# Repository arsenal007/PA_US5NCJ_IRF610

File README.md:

# PA_US5NCJ_IRF610
Power Amplifier US5NCJ

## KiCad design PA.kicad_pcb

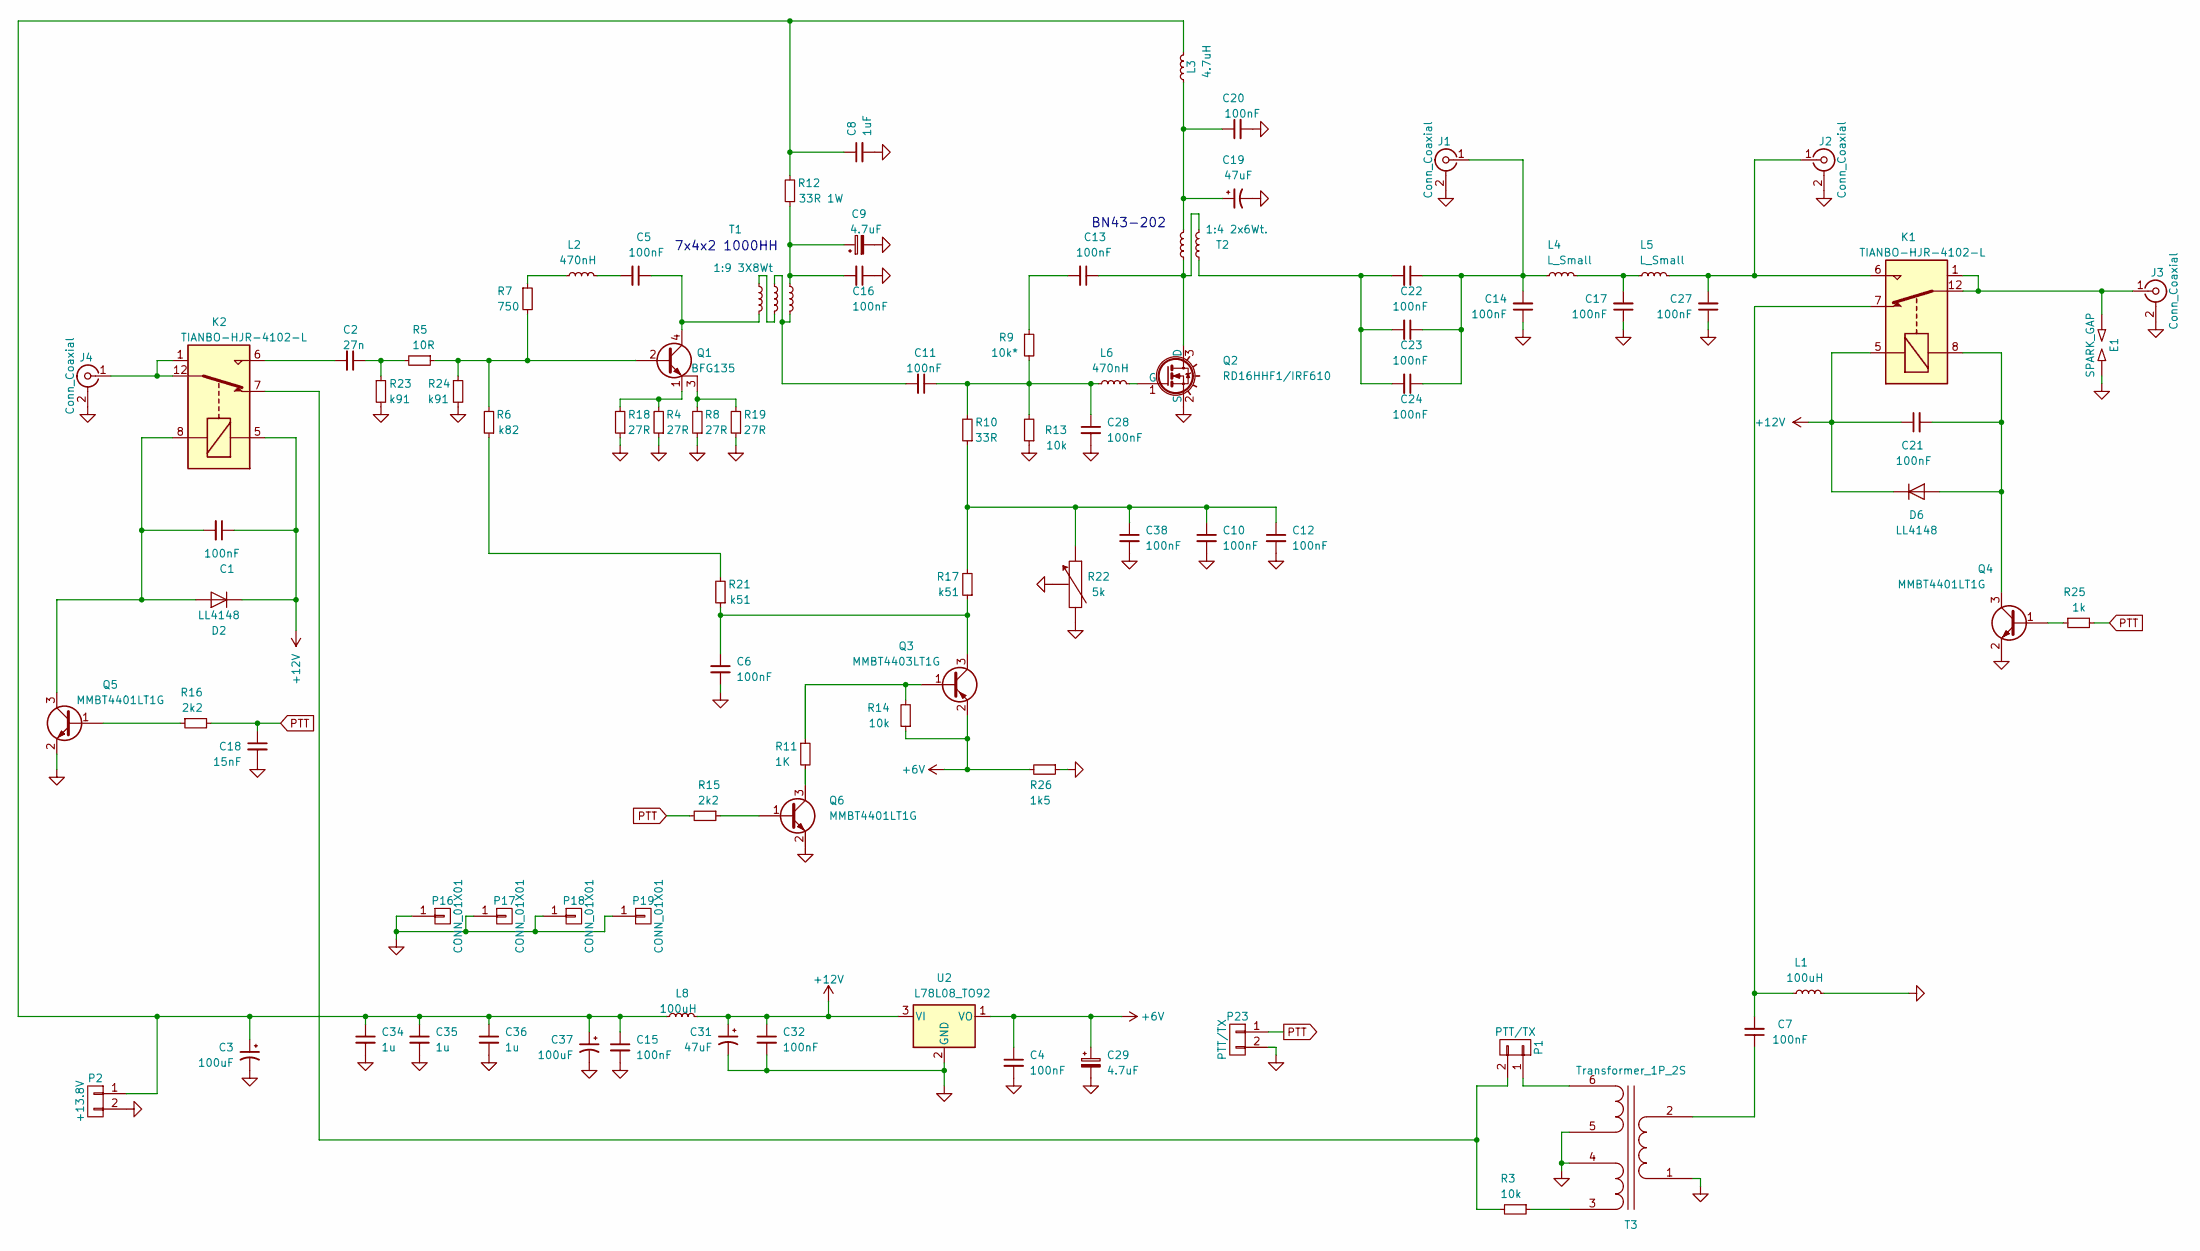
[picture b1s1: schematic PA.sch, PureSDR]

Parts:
C1, C4, C5, C6, C7, C10, C11, C12, C13, C14, C15, C16, C17, C20, C21, C22, C23, C24, C27, C28, C32, C38: 100nF; C_1206_0603
C2: 27n; C_1206_0603
C3, C37: 100uF; CP_Tantalum_Case-D_EIA-7343-31_Hand
C8: 1uF; C_1206_0603
C9, C29: 4.7uF; CP_Tantalum_Case-A_EIA-3216-18_Hand
C18: 15nF; C_1206_0603
C19, C31: 47uF; c_elec_6.3x7.7
C34, C35, C36: 1u; C_1206_0603
D2, D6: LL4148; MiniMELF_Handsoldering
E1: SPARK_GAP; Resistor_Horizontal_RM10mm
J1, J2, J3, J4: Conn_Coaxial; RFCONNECTOR
K1, K2: TIANBO-HJR-4102-L; Relay_SPDT_HJR-4102
L1, L8: 100uH; Resistor_SMD+THTuniversal_0805to2512_RM10_HandSoldering
L2, L6: 470nH; Resistor_SMD+THTuniversal_0805to2512_RM10_HandSoldering
L3: 4.7uH; Choke_CD54
L4, L5: L_Small; Choke_Toroid_horizontal_Diameter14mm_Amidon-T50
P1: PTT/TX; Pin_Header_Angled_1x02_Pitch2.54mm
P2: +13.8V; TerminalBlock_bornier-2_P5.08mm
P16, P17, P18, P19: CONN_01X01; MountingHole_3.2mm_M3_ISO7380_Pad
P23: PTT/TX; Pin_Header_Straight_1x02
Q1: BFG135; SOT-223
Q2: RD16HHF1/IRF610; RD16HHF1
Q3: MMBT4403LT1G; SOT-23_Handsoldering
Q4, Q5, Q6: MMBT4401LT1G; SOT-23_Handsoldering
R3, R13, R14: 10k; R_1206_0603
R4, R8, R18, R19: 27R; R_1206_0603
R5: 10R; R_1206_0603
R6: k82; R_1206_0603
R7: 750; R_1206_0603
R9: 10k*; Resistor_SMD+THTuniversal_0805to2512_RM10_HandSoldering
R10: 33R; R_1206_0603
R11: 1K; R_1206_0603
R12: 33R 1W; Resistor_SMD+THTuniversal_0805to2512_RM10_HandSoldering
R15, R16: 2k2; R_1206_0603
R17, R21: k51; R_1206_0603
R22: 5k; Potentiometer_Bourns_3296W_3-8Zoll_Inline_ScrewUp
R23, R24: k91; R_1206_0603
R25: 1k; R_1206_0603
R26: 1k5; R_1206_0603
T1: 1:9 3X8Wt; HF12
T2: 1:4 2x6Wt.; TRANSF1_4
T3: Transformer_1P_2S; Transf1_9
U2: L78L08_TO92; TO-92_Inline_Wide

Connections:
+6V: C4.1, C29.1, Q3.2 (E), R14.1, R26.2, U2.1 (VO)
+12V: C1.1, C21.1, C31.1, C32.1, D2.1 (K), D6.1 (K), K1.5, K2.5, L8.2, U2.3 (VI)
GND: C3.2, C4.2, C6.2, C8.2, C9.2, C10.2, C12.2, C14.1, C15.2, C16.1, C17.1, C18.2, C19.2, C20.2, C27.1, C28.2, C29.2, C31.2, C32.2, C34.2, C35.2, C36.2, C37.2, C38.2, E1.2, J1.2 (Ext), J2.2 (Ext), J3.2 (Ext), J4.2 (Ext), L1.2, P2.2, P16.1, P17.1, P18.1, P19.1, P23.2, Q2.2 (S), Q4.2 (E), Q5.2 (E), Q6.2 (E), R4.1, R8.1, R13.1, R18.1, R19.1, R22.2, R22.3, R23.2, R24.2, R26.1, T3.1 (AA), T3.4 (SB), T3.5 (SC), U2.2 (GND)
unnamed: C1.2, D2.2 (A), K2.8, Q5.3 (C)
unnamed: C2.1, R5.2, R23.1
unnamed: C2.2, K2.6
unnamed: C5.1, Q1.4 (C), T1.2
unnamed: C5.2, L2.2
unnamed: C6.1, Q3.3 (C), R17.1, R21.1
unnamed: C7.1, T3.2 (AB)
unnamed: C7.2, K1.7, L1.1
unnamed: C10.1, C12.1, C38.1, R10.1, R17.2, R22.1
unnamed: C11.1, C28.1, L6.1, R9.2, R10.2, R13.2
unnamed: C11.2, T1.3, T1.6
unnamed: C13.1, Q2.3 (D), T2.2, T2.3
unnamed: C13.2, R9.1
unnamed: C14.2, C22.1, C23.1, C24.1, J1.1 (In), L4.1
unnamed: C3.1, C8.1, C15.1, C34.1, C35.1, C36.1, C37.1, L3.2, L8.1, P2.1, R12.2
unnamed: C9.1, C16.2, R12.1, T1.5
unnamed: C17.2, L4.2, L5.1
unnamed: C19.1, C20.1, L3.1, T2.4
unnamed: C21.2, D6.2 (A), K1.8, Q4.3 (C)
unnamed: C22.2, C23.2, C24.2, T2.1
unnamed: C27.2, J2.1 (In), K1.6, L5.2
unnamed: E1.1, J3.1 (In), K1.1, K1.12
unnamed: J4.1 (In), K2.1, K2.12
unnamed: K2.7, P1.2, R3.2
unnamed: L2.1, R7.1
unnamed: L6.2, Q2.1 (G)
unnamed: P1.1, T3.6 (SD)
unnamed: Q1.1 (E), R4.2, R18.2
unnamed: Q1.2 (B), R5.1, R6.2, R7.2, R24.1
unnamed: Q1.3 (C), R8.2, R19.2
unnamed: Q3.1 (B), R11.1, R14.2
unnamed: Q4.1 (B), R25.1
unnamed: Q5.1 (B), R16.1
unnamed: Q6.1 (B), R15.1
unnamed: Q6.3 (C), R11.2
unnamed: R3.1, T3.3 (SA)
unnamed: R6.1, R21.2
unnamed: T1.1, T1.4
PTT: C18.1, P23.1, R15.2, R16.2, R25.2

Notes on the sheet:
BN43-202
7x4x2 1000HH

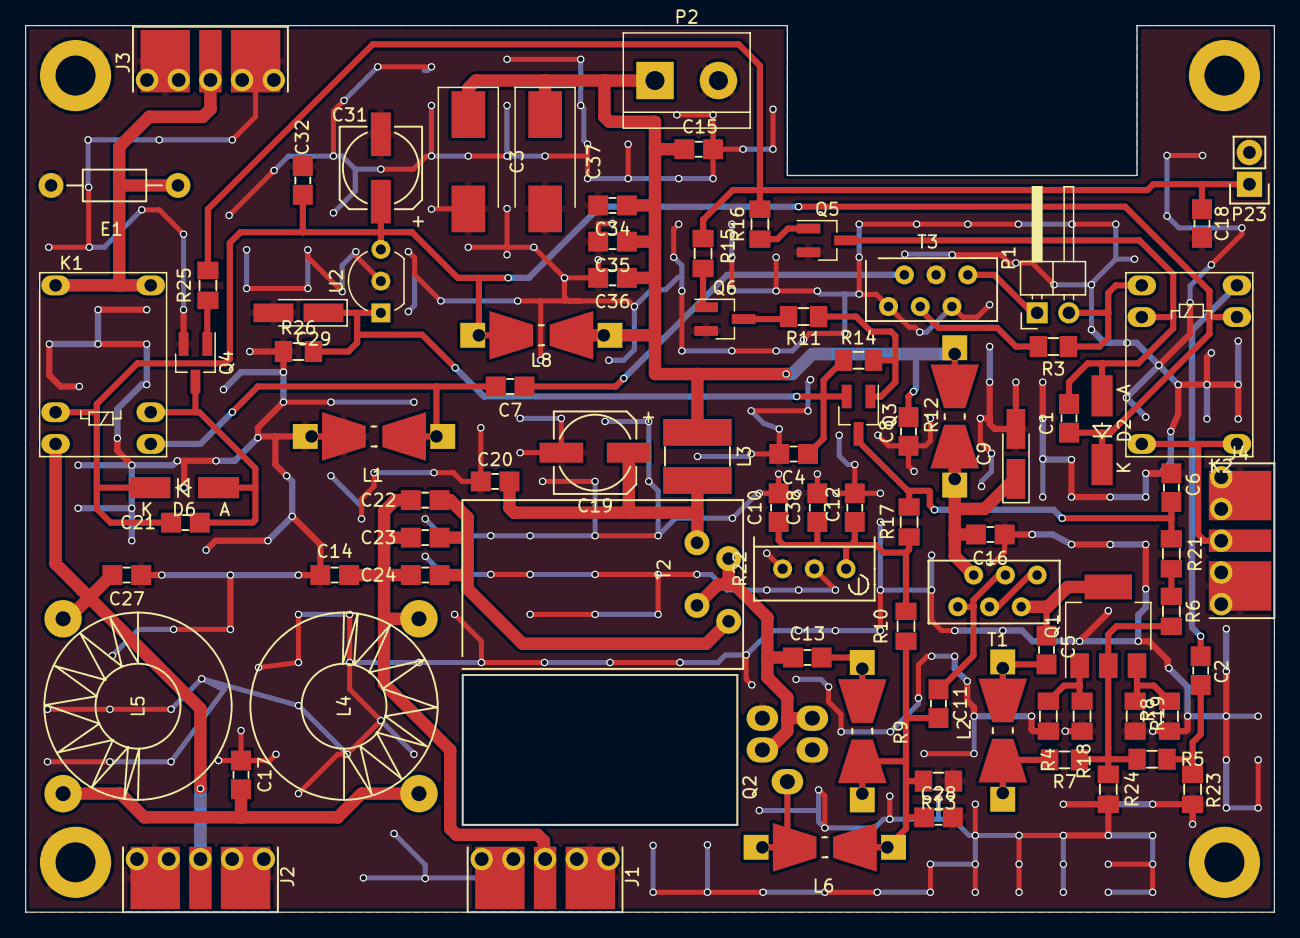
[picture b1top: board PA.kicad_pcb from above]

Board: 2 copper layers, 100.0 x 71.0 mm, 90 parts (0 on the bottom side), 42 nets.

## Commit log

2019-01-13 add gerber and libs
